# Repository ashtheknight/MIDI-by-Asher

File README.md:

# MIDI by Asher

**MIDI by Asher** is a custom MIDI controller designed in KiCad. The goal of this project is to build a compact controller with different types of inputs that can be used to control music software and MIDI-compatible instruments.

## Features

- 3 slide potentiometers for continuous control
- 1 EC11 rotary encoder
- 3 SK6812 MINI-E RGB LEDs
- 2 Kailh Choc low-profile mechanical switches
- 7 capacitive touch keys
- Waveshare ESP32-S3-Zero microcontroller

## Design

The schematic and PCB were designed in KiCad. The controller combines physical switches, touch inputs, rotary control, and sliders into one custom board.

### PCB Design

### Schematic

## Hardware

The main controller is the Waveshare ESP32-S3-Zero. The components are designed to provide several different ways to interact with MIDI software. Firmware and input mapping will determine how each control behaves.

## Project Files

The `PCB` folder contains the KiCad project files, including the schematic, PCB layout, and project settings.

## Notes

Firmware will be completed once parts arrive

### Disclaimer
AI was used to help organize information in the READ ME. all ideas writing and pretty much everything was done by me

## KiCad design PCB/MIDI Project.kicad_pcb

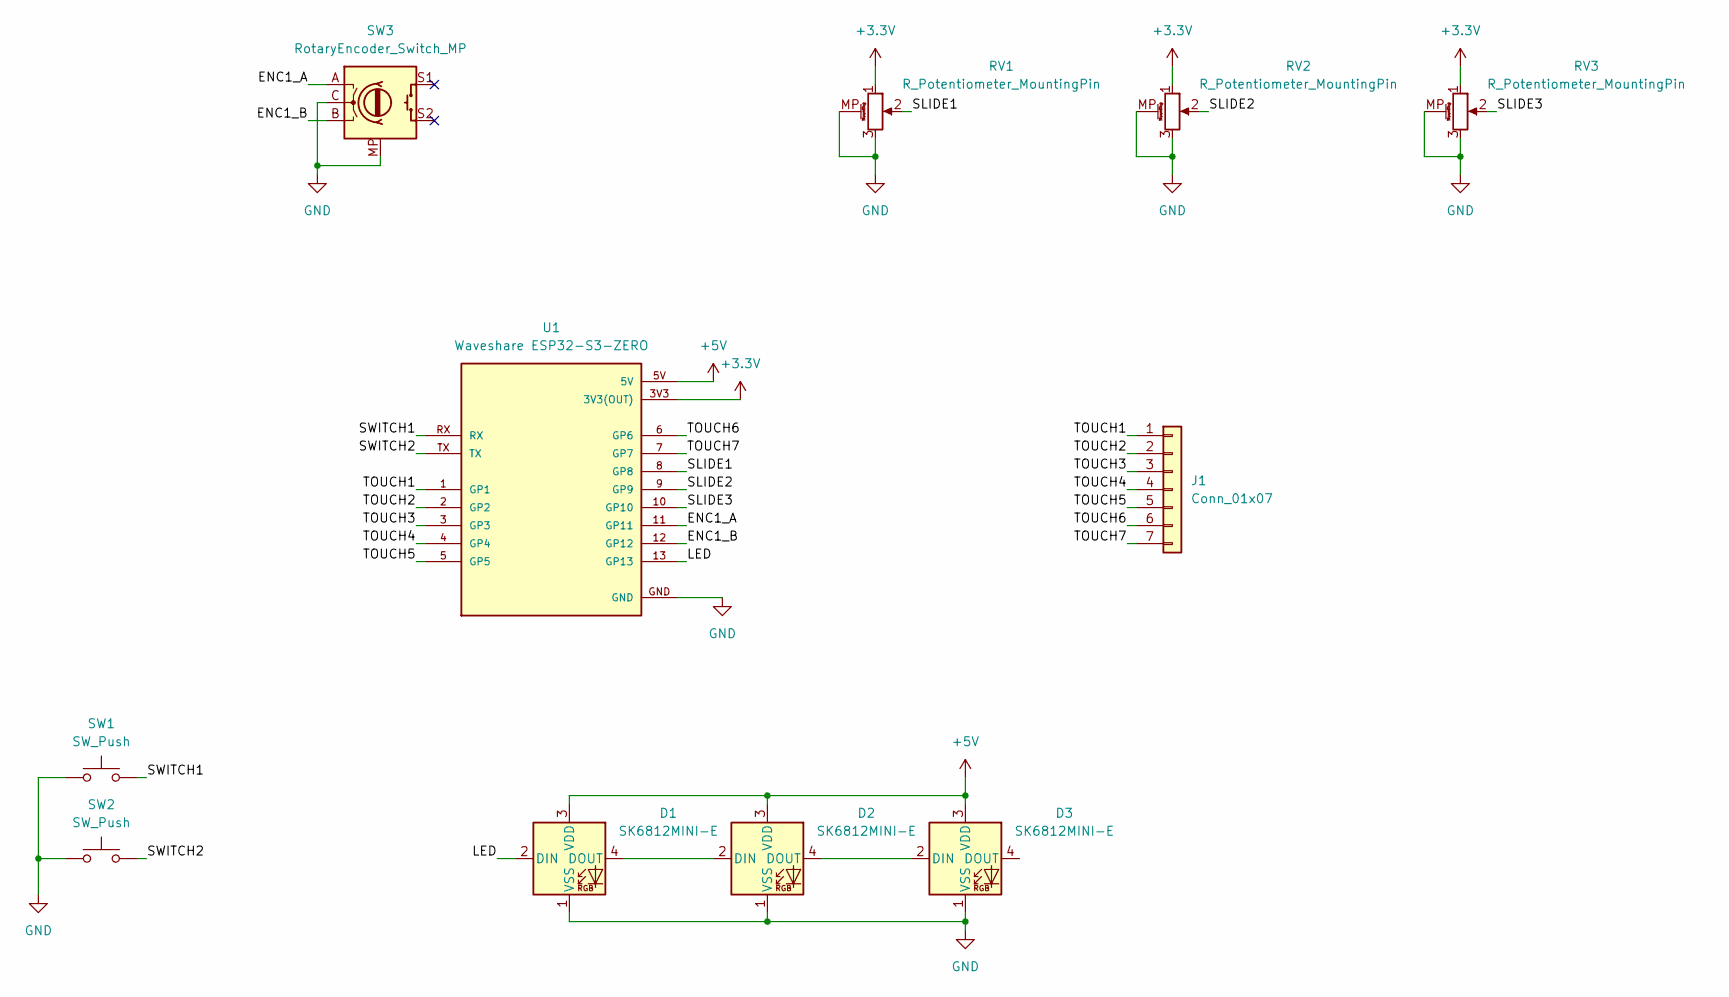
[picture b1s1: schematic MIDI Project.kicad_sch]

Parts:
D1, D2, D3: SK6812MINI-E; LED_SK6812MINI-E_3.2x2.8mm_P1.5mm_ReverseMount
J1: Conn_01x07; Capacitive Keys
RV1, RV2, RV3: R_Potentiometer_MountingPin; Potentiometer_Bourns_PTA1543_Single_Slide
SW1, SW2: SW_Push; Kailh Choc Low-Profile Switches
SW3: RotaryEncoder_Switch_MP; RotaryEncoder_Alps_EC11E-Switch_Vertical_H20mm
U1: Waveshare ESP32-S3-ZERO; Waveshare ESP32-S3-Zero; PARTREV NA

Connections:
+3.3V: RV1.1, RV2.1, RV3.1, U1.3V3 (3V3(OUT))
+5V: D1.3 (VDD), D2.3 (VDD), D3.3 (VDD), U1.5V
/ENC1_A: SW3.A, U1.11 (GP11)
/ENC1_B: SW3.B, U1.12 (GP12)
/LED: D1.2 (DIN), U1.13 (GP13)
/SLIDE1: RV1.2, U1.8 (GP8)
/SLIDE2: RV2.2, U1.9 (GP9)
/SLIDE3: RV3.2, U1.10 (GP10)
/SWITCH1: SW1.2, U1.RX
/SWITCH2: SW2.2, U1.TX
/TOUCH1: J1.1, U1.1 (GP1)
/TOUCH2: J1.2, U1.2 (GP2)
/TOUCH3: J1.3, U1.3 (GP3)
/TOUCH4: J1.4, U1.4 (GP4)
/TOUCH5: J1.5, U1.5 (GP5)
/TOUCH6: J1.6, U1.6 (GP6)
/TOUCH7: J1.7, U1.7 (GP7)
GND: D1.1 (VSS), D2.1 (VSS), D3.1 (VSS), RV1.3, RV1.MP (MountPin), RV2.3, RV2.MP (MountPin), RV3.3, RV3.MP (MountPin), SW1.1, SW2.1, SW3.C, SW3.MP, U1.GND
unnamed: D1.4 (DOUT), D2.2 (DIN)
unnamed: D2.4 (DOUT), D3.2 (DIN)

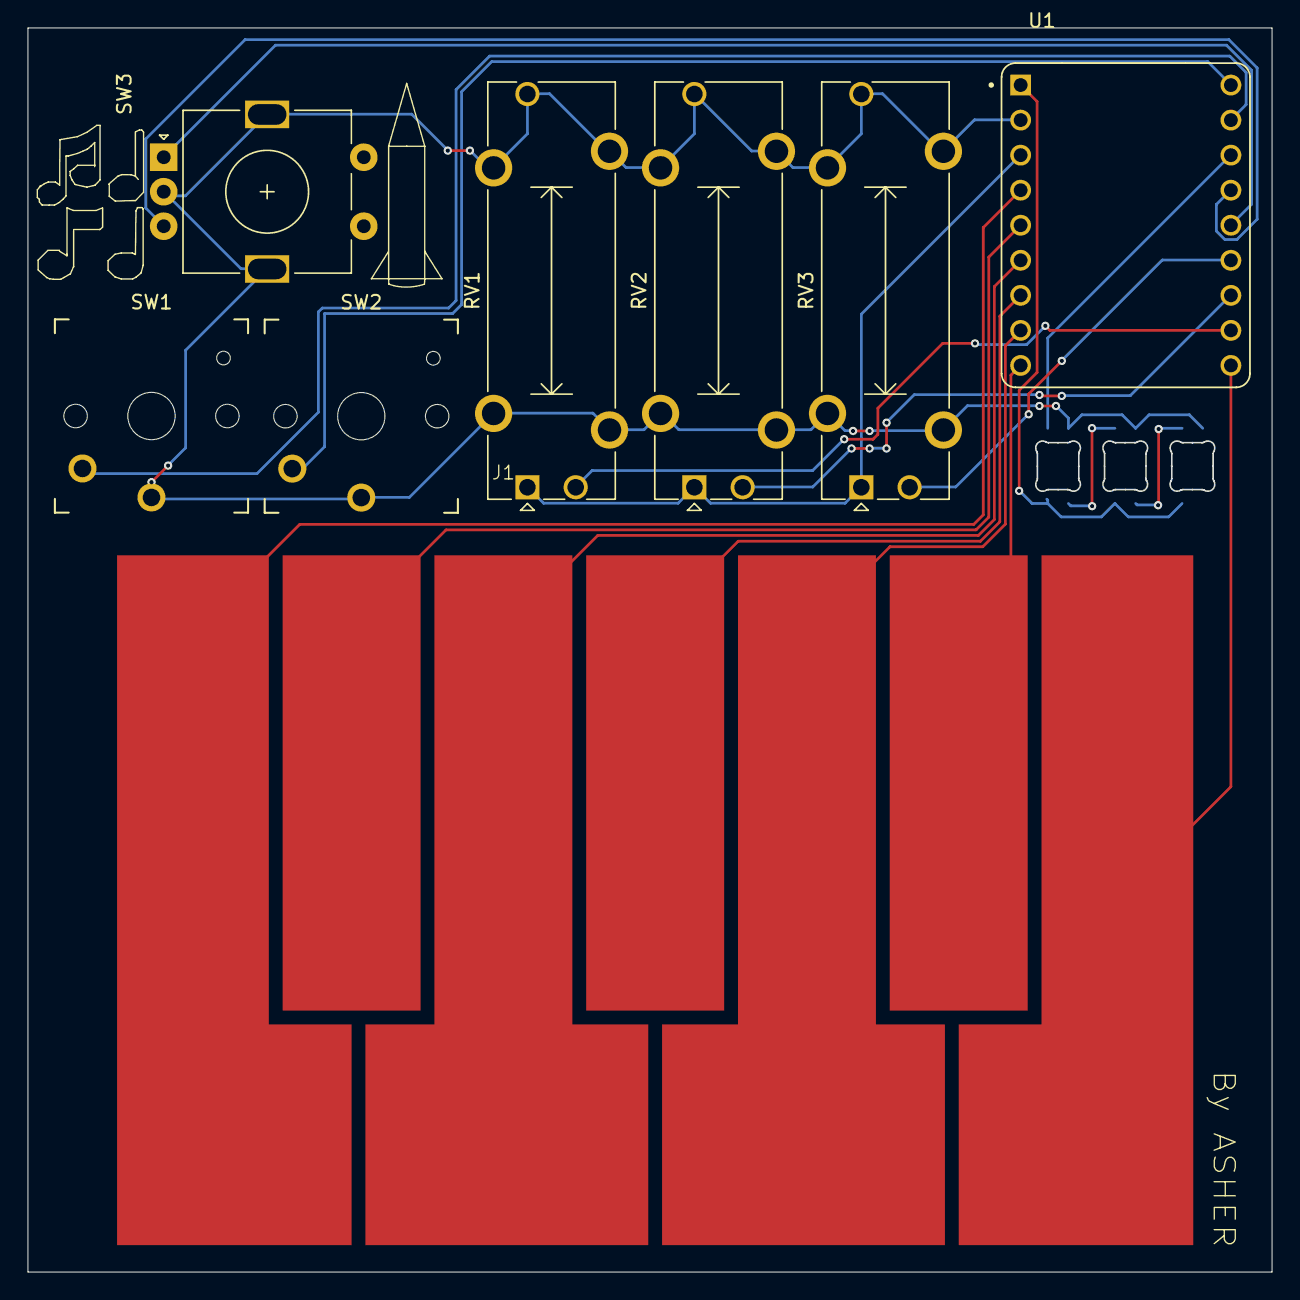
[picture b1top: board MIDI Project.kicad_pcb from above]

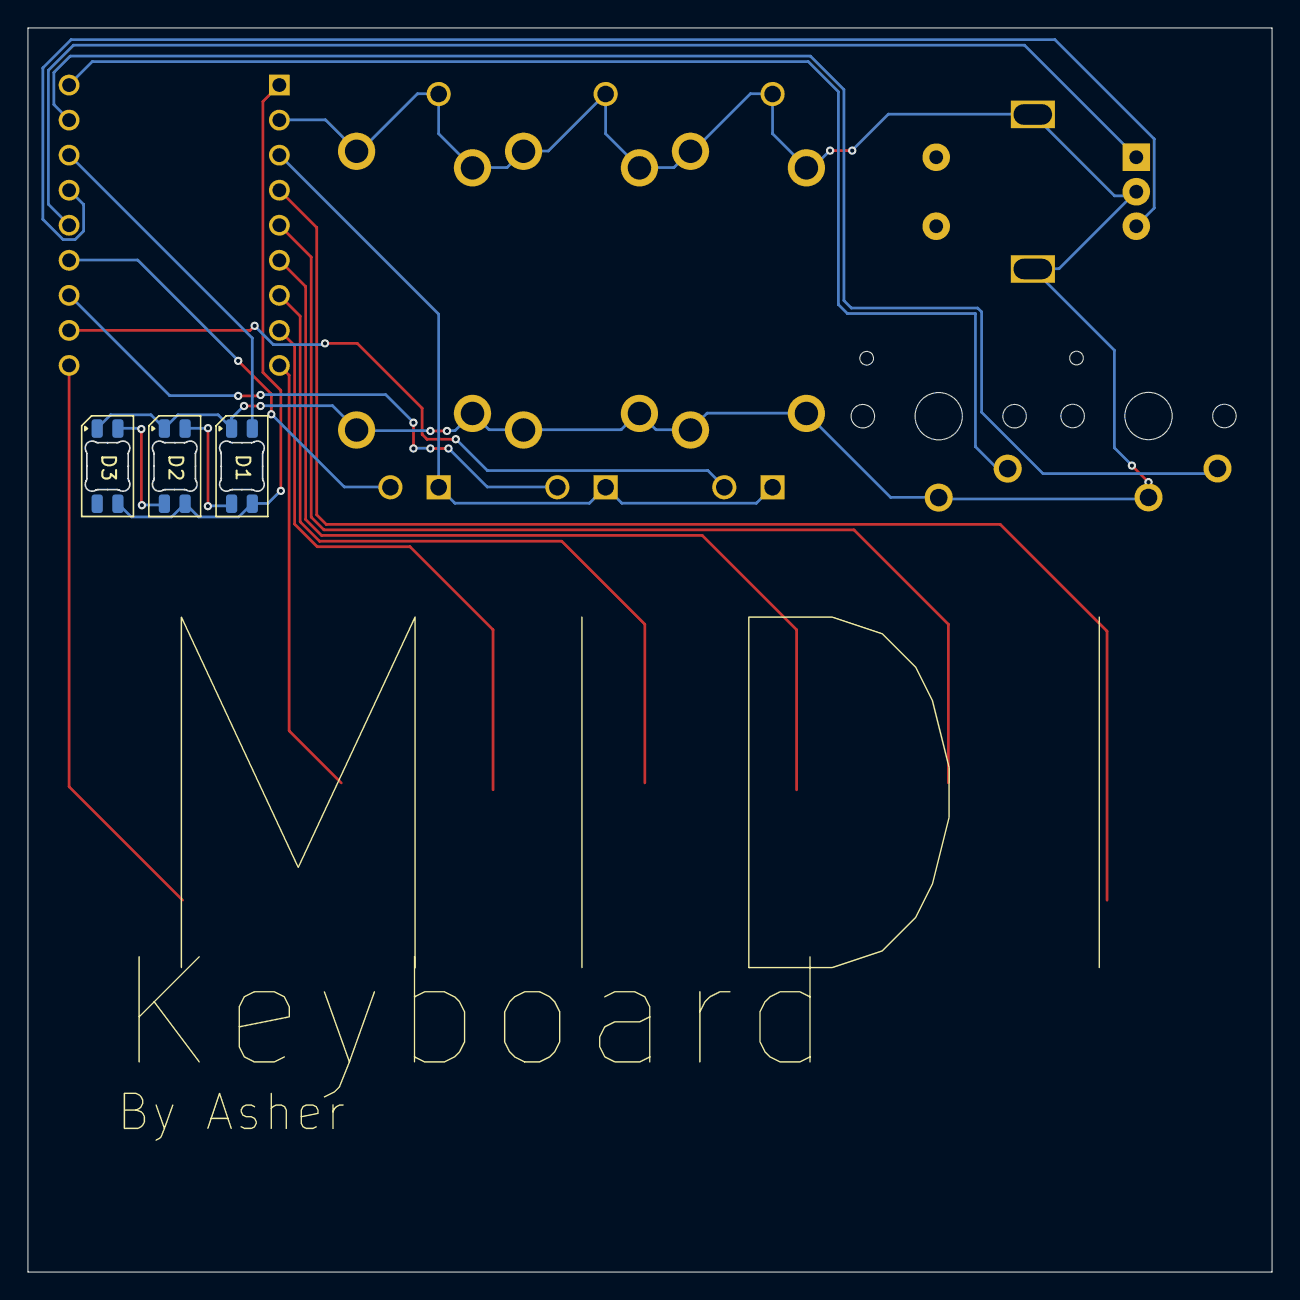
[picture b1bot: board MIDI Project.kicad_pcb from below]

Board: 2 copper layers, 90.2 x 90.2 mm, 11 parts (3 on the bottom side), 20 nets.

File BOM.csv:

Designator,Footprint,Quantity,Value,Total Cost,Part
"D1, D2, D3",LED_SK6812MINI-E_3.2x2.8mm_P1.5mm_ReverseMount,3,SK6812MINI-E,$3.36,https://www.aliexpress.us/item/3256807677321116.html
J1,Capacitive Keys,1,Capacitive Touch Buttons,,
"RV1, RV2, RV3",Potentiometer_Bourns_PTA1543_Single_Slide,3,Slider,$8.22,https://www.digikey.ca/en/products/detail/bourns-inc/PTA1543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
"SW1, SW2",Kailh Choc V2 Low-Profile Switches,2,SW_Push,$2.43,https://www.aliexpress.com/item/1005008883418065.html
SW3,RotaryEncoder_Alps_EC11E-Switch_Vertical_H20mm,1,RotaryEncoder_Switch_MP,$1.42,https://www.aliexpress.com/item/1005005193716172.html
U1,Waveshare ESP32-S3-Zero,1,Waveshare ESP32-S3-ZERO,$6.62,https://www.aliexpress.com/item/1005007004089798.html
,,,,,
,,,Total AliExpress:,$13.83,
,,,Total DigiKey:,$20.57,
,,,Total:,$46.69,
,,,Total including PCB:,$46.69 + $29.27,
,,,Grand Total:,$75.96,
